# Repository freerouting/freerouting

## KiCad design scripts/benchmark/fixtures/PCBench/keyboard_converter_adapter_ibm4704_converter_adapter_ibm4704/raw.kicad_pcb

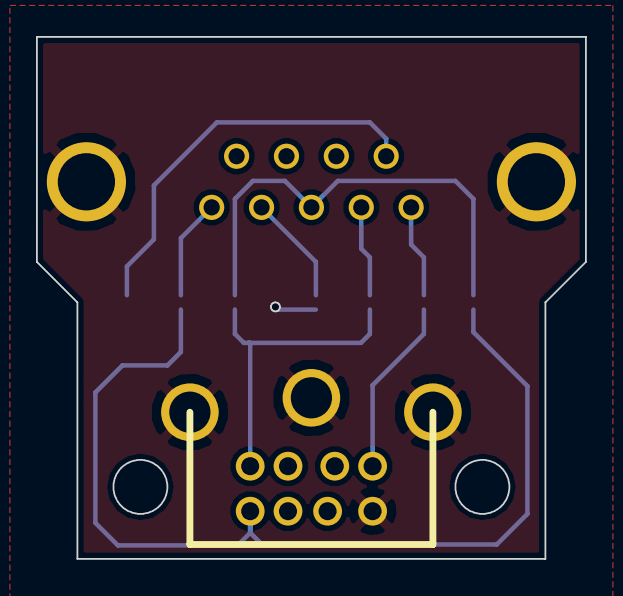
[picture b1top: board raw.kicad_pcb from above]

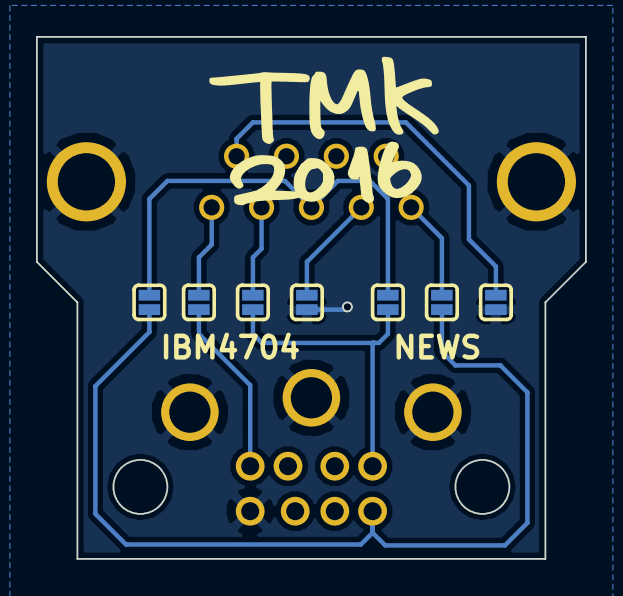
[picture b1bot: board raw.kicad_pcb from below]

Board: 2 copper layers, 30.5 x 29.0 mm, 9 parts (7 on the bottom side), 10 nets.

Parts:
CN1: MINI_DIN_8P_JACK; MINI_DIN_8
P1: CONN_01X10; DSUB9P
SJ1, SJ2, SJ3, SJ4, SJ5, SJ6, SJ7: SOLDER_JUMPER; SOLDER_JUMPER_2

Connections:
/D0: CN1.3, SJ3.1, SJ6.1
/D1: CN1.5, SJ4.1
/DS_1: P1.1, SJ5.2
/DS_2: P1.2, SJ1.2
/DS_3: P1.3, SJ2.2, SJ6.2
/DS_4: P1.4, SJ3.2
/DS_5: P1.5, SJ4.2
/DS_9: P1.9, SJ7.2
/VCC: CN1.6, SJ2.1, SJ5.1
GND: CN1.8, CN1.9, P1.10, SJ1.1, SJ7.1

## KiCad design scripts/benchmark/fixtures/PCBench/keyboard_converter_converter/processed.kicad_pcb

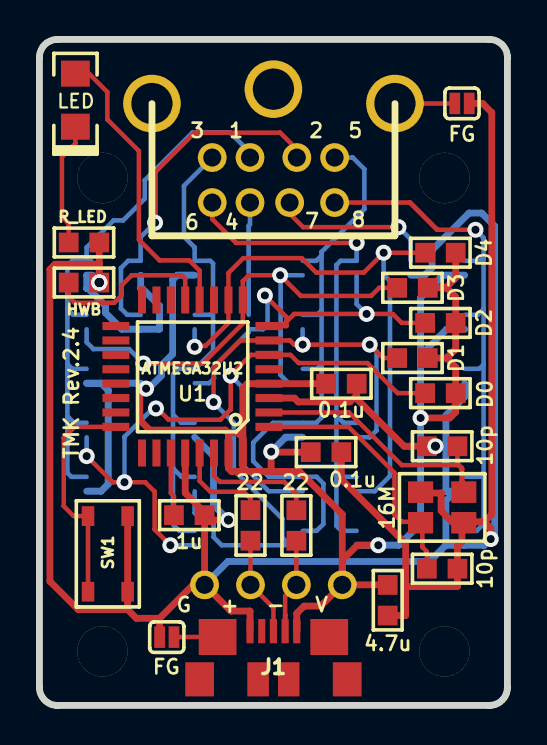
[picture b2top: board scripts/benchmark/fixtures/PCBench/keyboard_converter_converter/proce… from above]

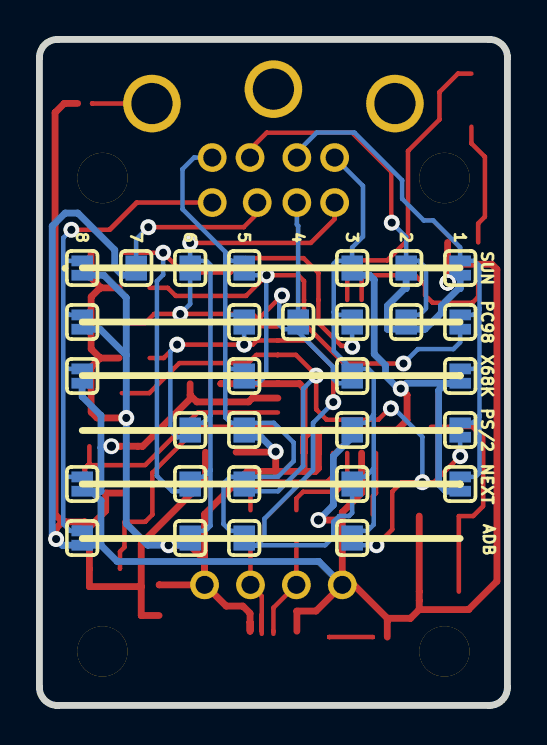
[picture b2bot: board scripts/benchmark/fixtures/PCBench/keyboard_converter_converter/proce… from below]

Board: 2 copper layers, 26.0 x 37.0 mm, 61 parts (30 on the bottom side), 28 nets.

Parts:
C1: 4.7u; C_1608
C2: 1u; C_1608
C3, C4: 0.1u; C_1608
C5, C6: 10p; C_1608
CN1: MINI_DIN_8P_JACK; MINI_DIN_8
D1: LED; LED_3020_REFLOW
HOLE_M2.6, HOLE_M2.6_2, HOLE_M2.6_3, HOLE_M2.6_4: VAL**; HOLE_M2.6
J1: USB_mini_micro_B; USB_microB
P1, P2, P3, P4: CONN_1; PIN_1
R1, R2: 22; R_1608
R3: 1k; R_1608
R4: R_LED; R_1608
R10, R11, R12, R13, R14: 1K; R_1608
SJ1, SJ2, SJ3, SJ4, SJ5, SJ6, SJ7, SJ8, SJ9, SJ10, SJ11, SJ12, SJ13, SJ14, SJ15, SJ16, SJ17, SJ18, SJ19, SJ20, SJ21, SJ22, SJ23, SJ24, SJ25, SJ26, SJ27, SJ28, SJ29, SJ30, SJ98, SJ99: SOLDER_JUMPER; SOLDER_JUMPER_2
SW1: SW_PUSH; SW_ALPS_SKRP
U1: ATMEGA32U2; QFP32
X1: 16M; FA-238

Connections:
+5V: C1.1, C3.1, C4.1, J1.1, P1.1, R10.1, R11.1, R12.1, R13.1, R14.1, SJ3.2, SJ5.2, SJ8.2, SJ18.2, SJ24.2, SJ26.2, SJ27.2, U1.4, U1.31, U1.32
/D+: J1.3, P3.1, R2.2
/D-: J1.2, P2.1, R1.2
/DIN1: CN1.1, SJ1.1, SJ2.1, SJ3.1, SJ4.1, SJ5.1
/DIN2: CN1.2, SJ6.1, SJ7.1
/DIN3: CN1.3, SJ8.1, SJ9.1, SJ10.1, SJ11.1, SJ12.1, SJ13.1
/DIN4: CN1.4, SJ14.1
/DIN5: CN1.5, SJ15.1, SJ16.1, SJ17.1, SJ18.1, SJ19.1, SJ20.1
/DIN6: CN1.6, SJ21.1, SJ22.1, SJ23.1, SJ24.1
/DIN7: CN1.7, SJ25.1
/DIN8: CN1.8, SJ26.1, SJ27.1, SJ28.1, SJ29.1, SJ30.1
/PD0: R10.2, SJ4.2, SJ13.2, SJ19.2, U1.6
/PD1: R11.2, SJ12.2, SJ16.2, SJ20.2, SJ22.2, U1.7
/PD2: R12.2, SJ10.2, SJ14.2, SJ21.2, U1.8
/PD3: R13.2, SJ2.2, SJ15.2, SJ17.2, U1.9
/PD4: R14.2, SJ9.2, SJ23.2, U1.10
/PD6: D1.1, U1.12
/PD7: R3.2, U1.13
/~RESET: SW1.1, U1.24
GND: C1.2, C2.2, C3.2, C4.2, C5.2, C6.2, J1.5, P4.1, R3.1, R4.2, SJ1.2, SJ6.2, SJ7.2, SJ11.2, SJ25.2, SJ28.2, SJ29.2, SJ30.2, SJ98.1, SJ99.2, SW1.2, U1.3, U1.28, X1.3
unnamed: C2.1, U1.27
unnamed: C5.1, U1.1, X1.1
unnamed: C6.1, U1.2, X1.2
unnamed: CN1.9, SJ99.1
unnamed: D1.2, R4.1
unnamed: J1.6, SJ98.2
unnamed: R1.1, U1.30
unnamed: R2.1, U1.29

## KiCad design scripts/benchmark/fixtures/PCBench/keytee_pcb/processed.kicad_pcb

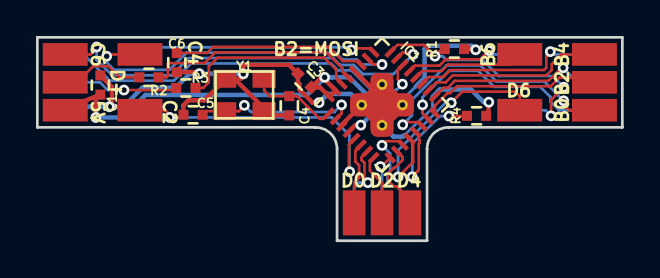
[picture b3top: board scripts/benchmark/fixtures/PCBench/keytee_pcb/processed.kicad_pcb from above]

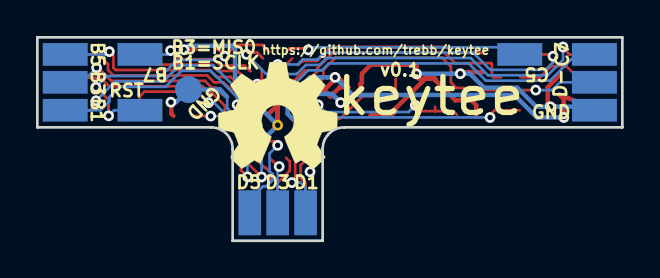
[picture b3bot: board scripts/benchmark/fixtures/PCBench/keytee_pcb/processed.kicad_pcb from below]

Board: 2 copper layers, 32.5 x 11.3 mm, 37 parts (13 on the bottom side), 31 nets.

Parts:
C1, C6: 1u; C_0402_square
C3: 100n; C_0402_square
C4, C5: 18p; C_0402_square
IC1: ATMEGA32U2; QFN-32-1EP_5x5mm_Pitch0.5mm_internal_vias
R1, R4: 10k; R_0402_square
R2, R3: 22; R_0402_square
W0, W1, W2, W3, W4, W5, W6, W7, W8, W15, W16, W17, W18, W19, W20, W21, W22, W23, W24, W25, W26, W27, W28, W29, W30: TEST_1P; SolderWirePad_SMD
W31: TEST_1P; SolderWirePad_SMD_circular
Y1: MT 16MHz; crystal_MT_32x25

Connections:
/B0: IC1.14, W0.1
/B1: IC1.15, W1.1
/B2: IC1.16, W2.1
/B3: IC1.17, W3.1
/B4: IC1.18, W15.1
/B5: IC1.19, W16.1
/B6: IC1.20, W17.1
/B7: IC1.21, W18.1
/C2: IC1.5, W26.1
/C4: IC1.26, W27.1
/C5: IC1.25, W28.1
/C6: IC1.23, W29.1
/C7: IC1.22, W30.1
/D0: IC1.6, W19.1
/D1: IC1.7, W20.1
/D2: IC1.8, W21.1
/D3: IC1.9, W22.1
/D4: IC1.10, W23.1
/D5: IC1.11, W24.1
/D6: IC1.12, W25.1
GND: C1.2, C3.2, C4.2, C5.2, C6.1, IC1.3, IC1.28, IC1.33, R4.1, W7.1, W31.1, Y1.3
unnamed: C4.1, IC1.1, Y1.1
unnamed: C5.1, IC1.2, Y1.2
unnamed: C6.2, IC1.27
unnamed: IC1.13, R4.2
unnamed: IC1.24, R1.2, W8.1
unnamed: IC1.29, R2.1
unnamed: IC1.30, R3.1
unnamed: R2.2, W4.1
unnamed: R3.2, W5.1
VCC: C1.1, C3.1, IC1.4, IC1.31, IC1.32, R1.1, W6.1
